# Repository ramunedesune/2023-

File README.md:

# 2023-robocon
２０２３年度のロボコンに向けた基板

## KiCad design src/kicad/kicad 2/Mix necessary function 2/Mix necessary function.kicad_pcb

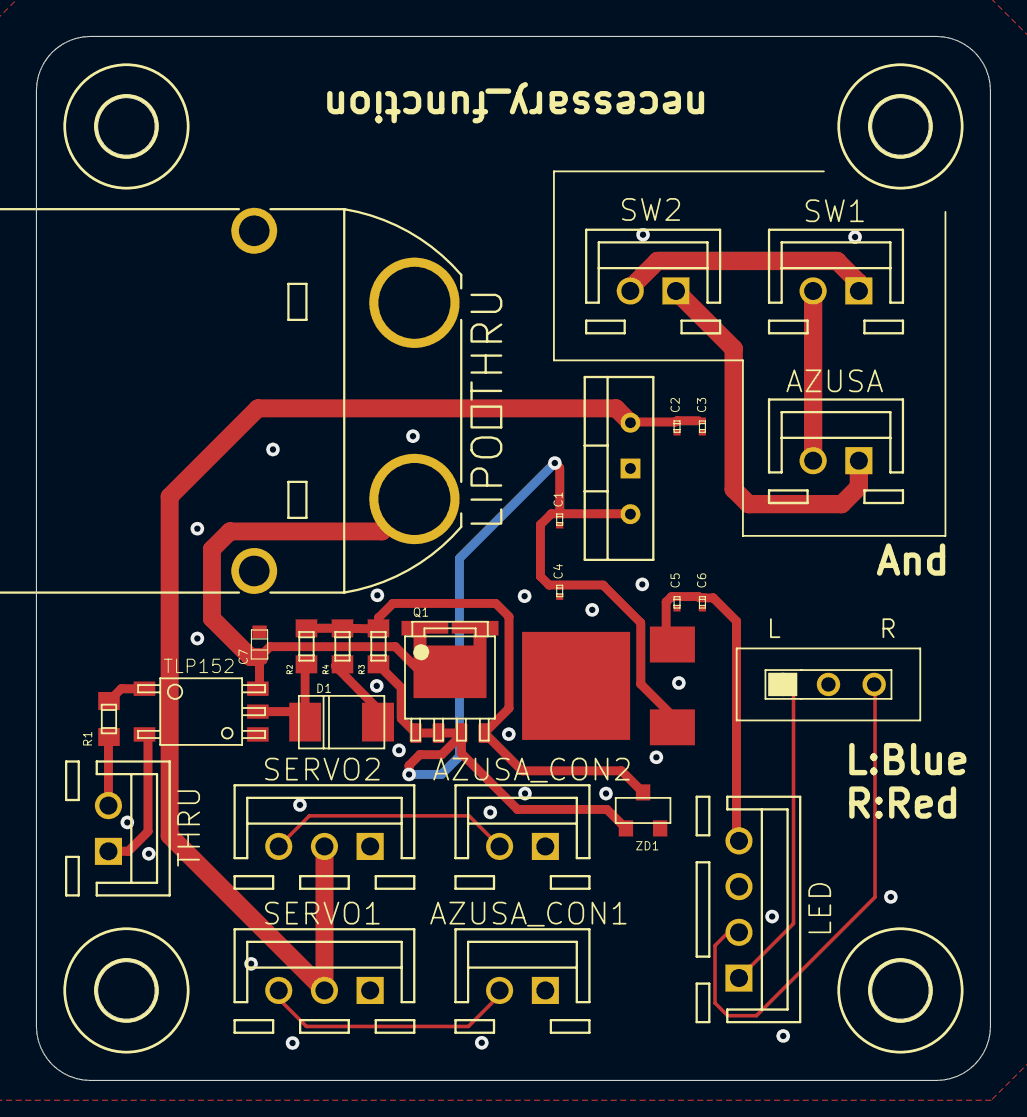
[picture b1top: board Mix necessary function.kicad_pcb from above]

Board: 2 copper layers, 53.0 x 58.0 mm, 32 parts (0 on the bottom side), 18 nets.

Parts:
AZUSA: 02-JST; B2B-XH
AZUSA_CON1, AZUSA_CON2: 02-JST; B2B-XH
C1, C4: 0.33μF; GRM0335C1E240GA01D
C2, C3, C5, C6: 0.1μF; GRM0335C1E240GA01D
C7: GCM188L81H104KA57
D1: GS2M-LTP
H1, H2, H3, H4: MOUNT-HOLE3.2; 3,2
LED: B4B-XH
LED_SW0: SS-12SDP2
LIPO＿THRU: XT90PW-M
Q1: SQJA16EP-T1_GE3
R1: 100; CR0603
R2: 820; CR0603
R3: 10; CR0603
R4: 10k; CR0603
SERVO1, SERVO2: B3B-XH
SW1, SW2: 02-JST; B2B-XH
THRU: 02-JST; B2B-XH
TLP1: TLP152
U$1: ＮＪＭ７８０６ＦＡ-6V
U$17: NJM7800SDL1-12V
ZD1: MMBZ5248B-TP

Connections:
+6V: C2.1, C3.1, SERVO1.2, SERVO2.2, U$1.OUTPUT
+12V: C5.1, C6.1, LED.4, U$17.VOUT
AGND: AZUSA.1, SW2.1
BLUE: LED.1, LED_SW0.L
EM: SW1.1, SW2.2
GND: AZUSA_CON1.1, AZUSA_CON2.1, C1.2, C2.2, C3.2, C4.2, C5.2, C6.2, C7.P$2, LED_SW0.C, LIPO＿THRU.-, SERVO1.1, SERVO2.1, TLP1.GND, U$1.GND, U$17.GND
unnamed: THRU.1, TLP1.CATHODE
unnamed: D1.C, R2.LEFT, TLP1.VO
unnamed: Q1.G, R2.RIGHT, R3.RIGHT, R4.RIGHT, ZD1.CATHODE
unnamed: D1.A, R3.LEFT
unnamed: C7.P$1, LIPO＿THRU.+, Q1.D, TLP1.VCC
unnamed: R1.LEFT, THRU.2
unnamed: R1.RIGHT, TLP1.ANODE
PVCC: C1.1, C4.1, Q1.S1, Q1.S2, Q1.S3, R4.LEFT, U$1.INPUT, U$17.VIN, ZD1.ANODE
PWM1_SERVO: AZUSA_CON1.2, SERVO1.3
PWM2_SERVO: AZUSA_CON2.2, SERVO2.3
RED: LED.2, LED_SW0.R
VCC: AZUSA.2, SW1.2

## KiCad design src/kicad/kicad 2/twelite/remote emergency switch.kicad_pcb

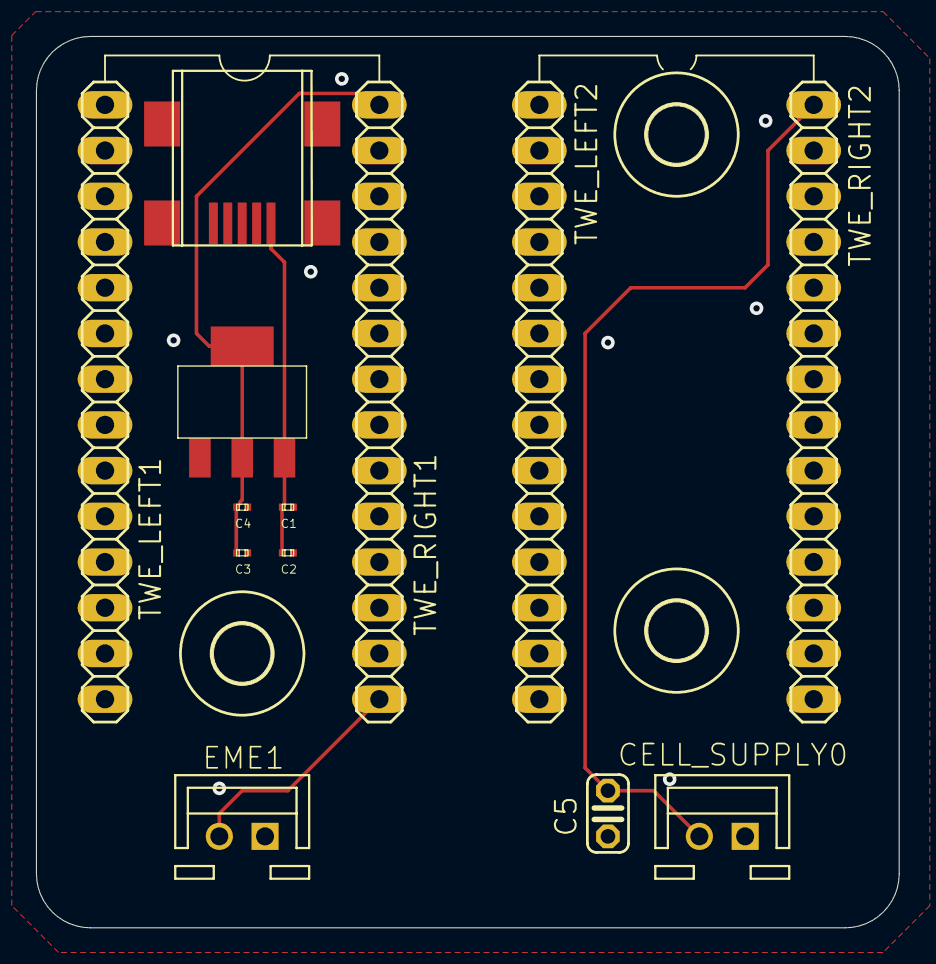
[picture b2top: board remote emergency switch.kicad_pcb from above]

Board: 2 copper layers, 47.9 x 49.5 mm, 16 parts (0 on the bottom side), 4 nets.

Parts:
C1, C2: 10μ; GRM0335C1E240GA01D
C3, C4: 22μ; GRM0335C1E240GA01D
C5: 0.1μ; C025-024X044
CELL_SUPPLY0: 02-JST; B2B-XH
DEVICE0: ＵＳＢコネクタ・ミニＢ(メス)
EME1: 02-JST; B2B-XH
H1, H2, H3: MOUNT-HOLE3.2; 3,2
REGYURETA0: ３．３V; ＡＺ１１１７ＣＨ－３．３ＴＲＧ１
TWE_LEFT1, TWE_LEFT2: 1X14
TWE_RIGHT1, TWE_RIGHT2: 1X14

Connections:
+3V3: C3.1, C4.1, C5.1, CELL_SUPPLY0.2, REGYURETA0.OUTPUT, REGYURETA0.VOUT, TWE_RIGHT1.1, TWE_RIGHT2.1
+5V: C1.1, C2.1, DEVICE0.VBUS, REGYURETA0.INPUT
EM1: EME1.2, TWE_RIGHT1.14
SGND: C1.2, C2.2, C3.2, C4.2, C5.2, CELL_SUPPLY0.1, DEVICE0.GND, EME1.1, REGYURETA0.ADJ/GND, TWE_LEFT1.1, TWE_LEFT2.1

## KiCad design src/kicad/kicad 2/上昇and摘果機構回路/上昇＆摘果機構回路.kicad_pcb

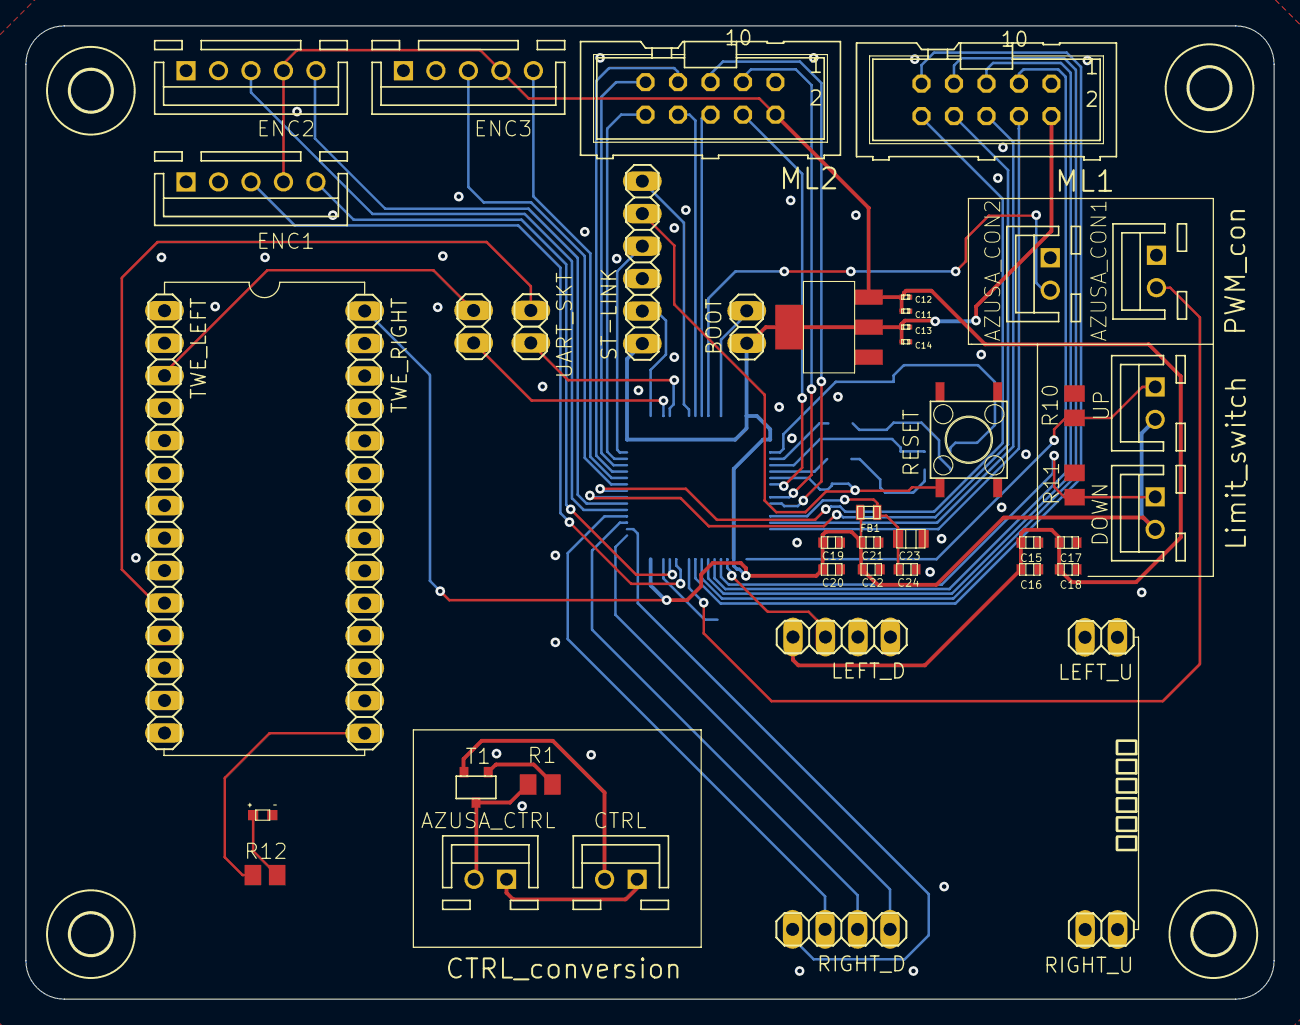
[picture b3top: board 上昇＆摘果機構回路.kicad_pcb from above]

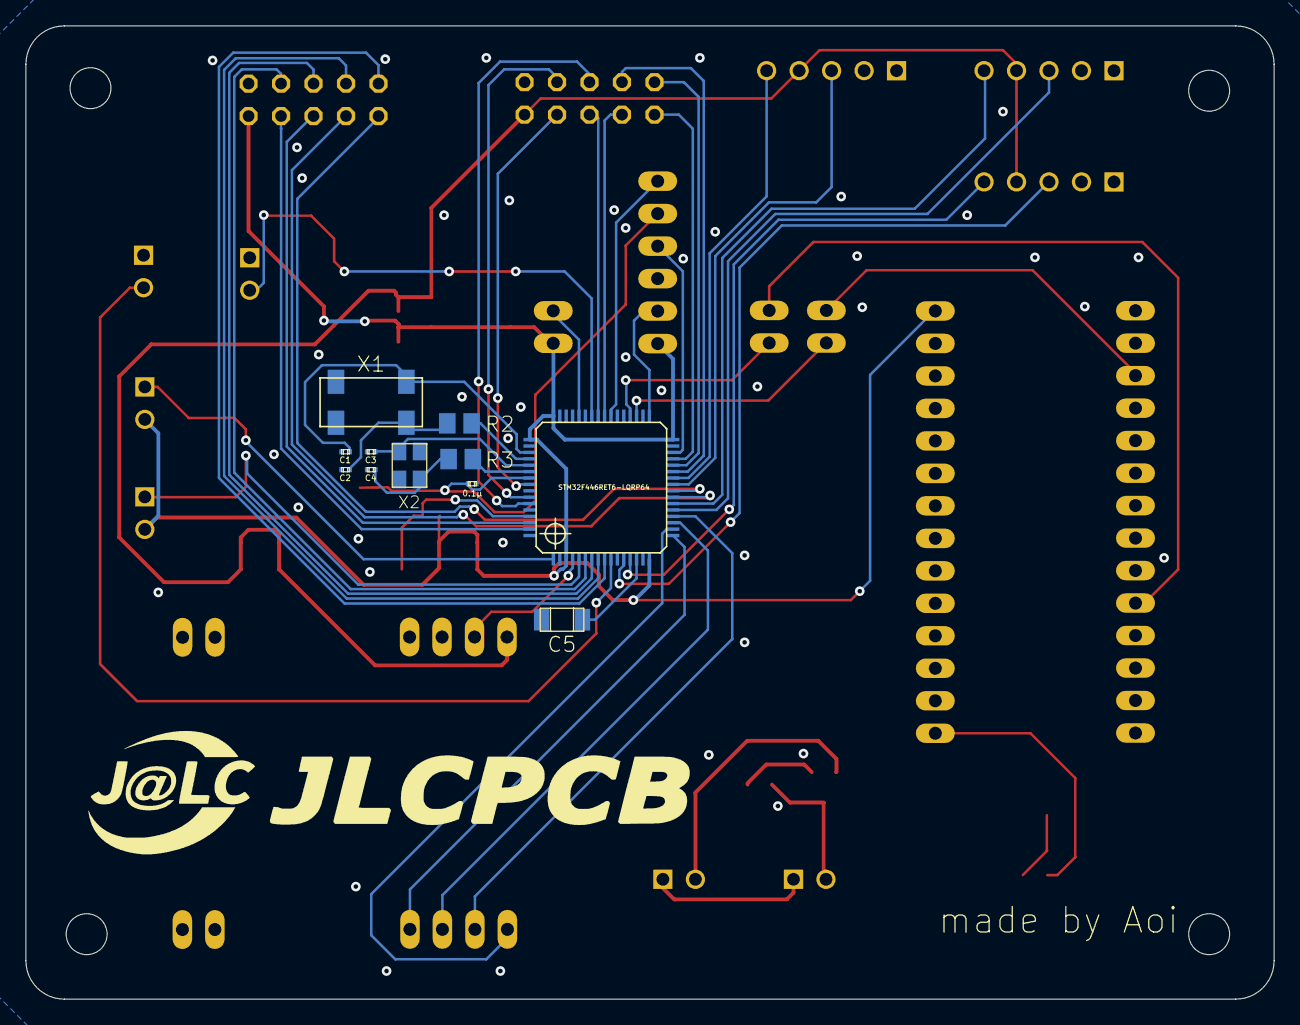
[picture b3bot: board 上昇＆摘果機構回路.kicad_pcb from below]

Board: 2 copper layers, 97.6 x 76.1 mm, 59 parts (11 on the bottom side), 57 nets.

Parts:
0.1μ: GRM0335C1E240GA01D
AZUSA_CON1, AZUSA_CON2: 02-JST; B2B-XH
AZUSA_CTRL: 02-JST; B2B-XH
BOOT: 1X02
C1, C2, C3, C4: GRM0335C1E240GA01D
C5: GRM31CR71H475KA12
C11, C12: 10μ; GRM0335C1E240GA01D
C13, C14: 22μ; GRM0335C1E240GA01D
C15, C16, C17, C18, C19, C20, C21, C22, C24: GCM188L81H104KA57
C23: GRM21BC72A105KE01
CTRL: 02-JST; B2B-XH
DOWN: 02-JST; B2B-XH
ENC1, ENC2, ENC3: B5B-XH
FB1: BLM18KG121TN1D
H1, H2, H3, H4: MOUNT-HOLE3.2; 3,2
LEFT_D: 1X04
LEFT_U: 1X02
ML1, ML2: ML10
PIN_SOCKET1, PIN_SOCKET2: 1X02
R1, R10, R11: 100; M0805
R2, R3: 0; M0805
R12: 150; M0805
REGYURETA0: ３．３V; ＡＺ１１１７ＣＨ－３．３ＴＲＧ１
RIGHT_D: 1X04
RIGHT_U: 1X02
ST-LINK: 1X06
T1: 2SC3325-Y,LF
TWE_LEFT: 1X14
TWE_RIGHT: 1X14
U$1: STM32F446RET6-LGRF64; STM32F446FRT6
U$2: TACTSWITCH
U$8: SMD1608チップLED
UP: 02-JST; B2B-XH
X1: 32.768K12.5PI/MC306; 32.768K12.5PI_MC306
X2: RH100-24.000-18-1020-EXT-TR

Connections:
+3V3: BOOT.1, C13.1, C14.1, C19.P$1, C20.P$1, C21.P$1, C22.P$1, DOWN.2, FB1.1, ML1.2, REGYURETA0.OUTPUT, REGYURETA0.VOUT, ST-LINK.1, TWE_RIGHT.1, U$1.VBAT, U$1.VDD1, U$1.VDD2, U$1.VDD3, U$1.VDD4, UP.2
+5V: C11.1, C12.1, C15.P$1, C16.P$1, C17.P$1, C18.P$1, ENC1.4, ENC2.4, ENC3.4, LEFT_D.4, ML2.2, REGYURETA0.INPUT
BOOT0: BOOT.2, U$1.BOOT0
COM_LED: LEFT_D.3, U$1.PA4
COM_LED2: R12.1, TWE_RIGHT.14
CS: RIGHT_D.1, U$1.PB12
DIR1: ML1.9, U$1.PC5
DIR2: ML1.7, U$1.PC4
DIR3: ML1.5, U$1.PA7
DIR4: ML1.3, U$1.PA6
EN1_A: ENC1.3, U$1.PB2
EN1_B: ENC1.5, U$1.PB10
EN2_A: ENC2.3, U$1.PC6
EN2_B: ENC2.5, U$1.PC7
EN3_A: ENC3.3, U$1.PA8
EN3_B: ENC3.5, U$1.PA9
LED1: ML2.4, U$1.PC0
LED2: ML2.6, U$1.PB5
LED3: ML2.8, U$1.PB4
LED4: ML2.10, U$1.PA12
LED5: ML2.9, U$1.PA11
LED6: ML2.7, U$1.PA10
LED7: ML2.5, U$1.PC3
LED8: ML2.3, U$1.PC2
MISO: RIGHT_D.2, U$1.PB14
MOSI: RIGHT_D.3, U$1.PB15
unnamed: C2.2, R2.2, X1.4
unnamed: C5.1, U$1.VCAP_1
unnamed: C1.2, U$1.PC14-OSC32_IN, X1.1
unnamed: C3.2, U$1.PH0-OSC_IN, X2.1
unnamed: C4.2, R3.2, X2.3
unnamed: R3.1, U$1.PH1-OSC_OUT
unnamed: R2.1, U$1.PC15-OSC32_OUT
unnamed: CTRL.2, T1.EMITTER
unnamed: AZUSA_CTRL.2, R1.1, T1.COLLECTOR
unnamed: R1.2, T1.BASE
unnamed: R12.2, U$8.ANODE
unnamed: C23.P$1, C24.P$1, FB1.2, U$1.VDDA/VREF+
NO1: R10.1, U$1.PA3, UP.1
NO2: DOWN.1, R11.1, U$1.PA5
NRST: 0.1μ.1, ST-LINK.5, U$1.NRST, U$2.P$1
PGND: AZUSA_CTRL.1, CTRL.1
PWM1: ML1.10, U$1.PC9
PWM1_SERVO: AZUSA_CON1.2, U$1.PB0
PWM2: ML1.8, U$1.PC8
PWM2_SERVO: AZUSA_CON2.2, U$1.PB6
PWM3: ML1.6, U$1.PA0
PWM4: ML1.4, U$1.PA1
RX: PIN_SOCKET1.2, TWE_LEFT.10
SCK: RIGHT_D.4, U$1.PB13
SGND: 0.1μ.2, AZUSA_CON1.1, AZUSA_CON2.1, C1.1, C2.1, C3.1, C4.1, C5.2, C11.2, C12.2, C13.2, C14.2, C15.P$2, C16.P$2, C17.P$2, C18.P$2, C19.P$2, C20.P$2, C21.P$2, C22.P$2, C23.P$2, C24.P$2, ENC1.1, ENC2.1, ENC3.1, LEFT_D.1, LEFT_U.1, LEFT_U.2, ML1.1, ML2.1, R10.2, R11.2, REGYURETA0.ADJ/GND, RIGHT_U.1, RIGHT_U.2, ST-LINK.3, TWE_LEFT.1, U$1.VSS1, U$1.VSS2, U$1.VSS3, U$1.VSS4, U$1.VSSA/VREF-, U$2.P$4, U$8.CATHODE, X2.2, X2.4
SWCLK: ST-LINK.2, U$1.PA14
SWDIO: ST-LINK.4, U$1.PA13
SWO: ST-LINK.6, U$1.PB3
TX: PIN_SOCKET2.2, TWE_LEFT.3
UART_RX: PIN_SOCKET1.1, U$1.PC11
UART_TX: PIN_SOCKET2.1, U$1.PC10

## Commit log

2023-09-11 2st commit
2023-09-12 1st fix
2023-09-12 3rd fix
2023-09-12 DRC fix
2023-09-13 twelite
2023-09-13 fix around twelite
2023-09-14 servo
2023-09-14 テープLED
2023-09-14 add serbo pin
2023-09-14 fix necefun
2023-09-14 silk update
2023-09-15 servo2
2023-09-15 servo3
2023-09-15 necefunc fix
2023-09-15 kicad necefunc
2023-09-15 fix twelite
2023-09-17 fix twelite circuit slot
2023-09-17 add servo emergency
